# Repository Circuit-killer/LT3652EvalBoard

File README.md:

# LT3652EvalBoard

BOM: https://octopart.com/bom-lookup/5VZMcxHE

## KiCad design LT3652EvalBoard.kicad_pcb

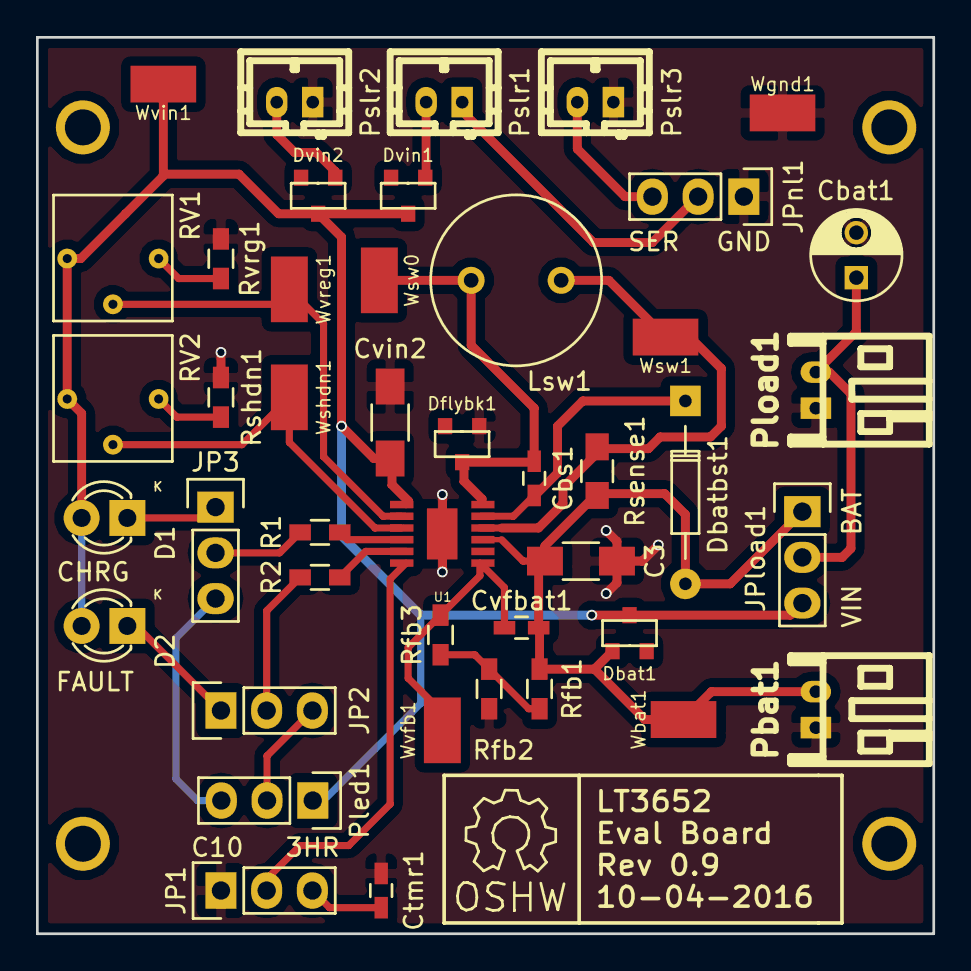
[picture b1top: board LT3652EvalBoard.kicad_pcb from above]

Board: 2 copper layers, 49.8 x 49.8 mm, 44 parts (0 on the bottom side), 27 nets.

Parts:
C3: 10uF; C_1206_HandSoldering
Cbat1: 100uF; C_Radial_D5_L6_P2.5
Cbs1: 1uF; C_0603_HandSoldering
Ctmr1: 0.68µF; C_0603_HandSoldering
Cvfbat1: 22pF; C_0603_HandSoldering
Cvin2: 10uF; C_1206_HandSoldering
D1: 3mm GRN; LED-3MM
D2: 3mm RED; LED-3MM
Dbat1: D_Schottky_Small_ZLLS500; DIODES_INC_ZLLS500
Dbatbst1: D_Small; Diode_DO-35_SOD27_Horizontal_RM10
Dflybk1: ZLLS500; DIODES_INC_ZLLS500
Dvin1, Dvin2: ZLLS500; DIODES_INC_ZLLS500
JP1: TIMER OPT; Pin_Header_Straight_1x03
JP2, JP3: JUMPER3; Pin_Header_Straight_1x03
JPload1: JUMPER3; Pin_Header_Straight_1x03
JPnl1: JUMPER3; Pin_Header_Straight_1x03
Lsw1: 10uH; PANASONIC_ELC09D100F
Pbat1: JST PH; s2b-ph-kl
Pled1: CONN_01X03; Pin_Header_Straight_1x03
Pload1: JST PH; s2b-ph-kl
Pslr1, Pslr2, Pslr3: JST PH; b2b-ph-kl
R1, R2: 10K; R_0603_HandSoldering
RV1, RV2: POT; Bourns_3362P_Trimmer
Rfb1: 90k; R_0603_HandSoldering
Rfb2: 330k; R_0603_HandSoldering
Rfb3: 179k; R_0603_HandSoldering
Rsense1: 250mO; R_0805_HandSoldering
Rshdn1: 10K; R_0603_HandSoldering
Rvrg1: 10K; R_0603_HandSoldering
U1: LT3652; LT3652MSE_HandSoldering
Wbat1: TEST_1P; HARWIN_S1751-46
Wgnd1: TEST_1P; HARWIN_S1751-46
Wshdn1: TEST_1P; HARWIN_S1751-46
Wsw0, Wsw1: TEST_1P; HARWIN_S1751-46
Wvfb1: TEST_1P; HARWIN_S1751-46
Wvin1: TEST_1P; HARWIN_S1751-46
Wvreg1: TEST_1P; HARWIN_S1751-46

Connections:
/BAT: C3.1, Cvfbat1.1, Dbat1.3, Dbatbst1.2, JPload1.1, Pbat1.2, Rfb1.1, Rsense1.2, U1.9, Wbat1.1
/BOOST: Cbs1.1, Dbatbst1.1, U1.11
/SENSE: Lsw1.2, Rsense1.1, U1.10, Wsw1.1
/SHDN: RV2.2, U1.3, Wshdn1.1
/SW: Cbs1.2, Dflybk1.1, Lsw1.1, U1.12, Wsw0.1
/VFB: Cvfbat1.2, Rfb3.2, U1.7, Wvfb1.1
/VIN: Cvin2.2, D1.2, D2.2, Dbat1.1, Dvin1.1, Dvin2.1, JPload1.3, Pled1.1, RV1.1, RV2.1, U1.1, Wvin1.1
/VIN_REG: RV1.2, U1.2, Wvreg1.1
GND: C3.2, Cbat1.2, Ctmr1.2, Cvin2.1, Dflybk1.3, JP1.1, JPnl1.1, Pbat1.1, Pload1.1, Pslr2.1, Pslr3.1, Rfb2.2, Rshdn1.2, Rvrg1.2, U1.13, Wgnd1.1
unnamed: Cbat1.1, JPload1.2, Pload1.2
unnamed: Ctmr1.1, JP1.3
unnamed: D1.1, JP3.1
unnamed: D2.1, JP2.1
unnamed: Dvin1.3, Pslr1.2
unnamed: Dvin2.3, Pslr2.2
unnamed: JP1.2, U1.6
unnamed: JP2.2, R2.2
unnamed: JP2.3, Pled1.2
unnamed: JP3.2, R1.2
unnamed: JP3.3, Pled1.3
unnamed: JPnl1.2, Pslr1.1
unnamed: JPnl1.3, Pslr3.2
unnamed: R1.1, U1.4
unnamed: R2.1, U1.5
unnamed: RV1.3, Rvrg1.1
unnamed: RV2.3, Rshdn1.1
unnamed: Rfb1.2, Rfb2.1, Rfb3.1

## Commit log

2016-03-15 Initial commit - Rev 0.3
2016-03-15 Fixed project info
2016-03-18 Rev 0.3 Final - onto Rev 0.4 now to make the board smaller hence cheaper to manufacture
2016-03-21 Upload of Rev 0.5
2016-03-24 Rev 0.6 - Adds ability to add solar panel in series, plus separate blocking diode for parallel solar panel
2016-03-24 Minor alignment fix
2016-03-24 Fixed wrong footprint for Rsense1
2016-03-29 Rev 0.7
2016-04-11 Rev 0.9
2017-03-17 Rev 0.10
